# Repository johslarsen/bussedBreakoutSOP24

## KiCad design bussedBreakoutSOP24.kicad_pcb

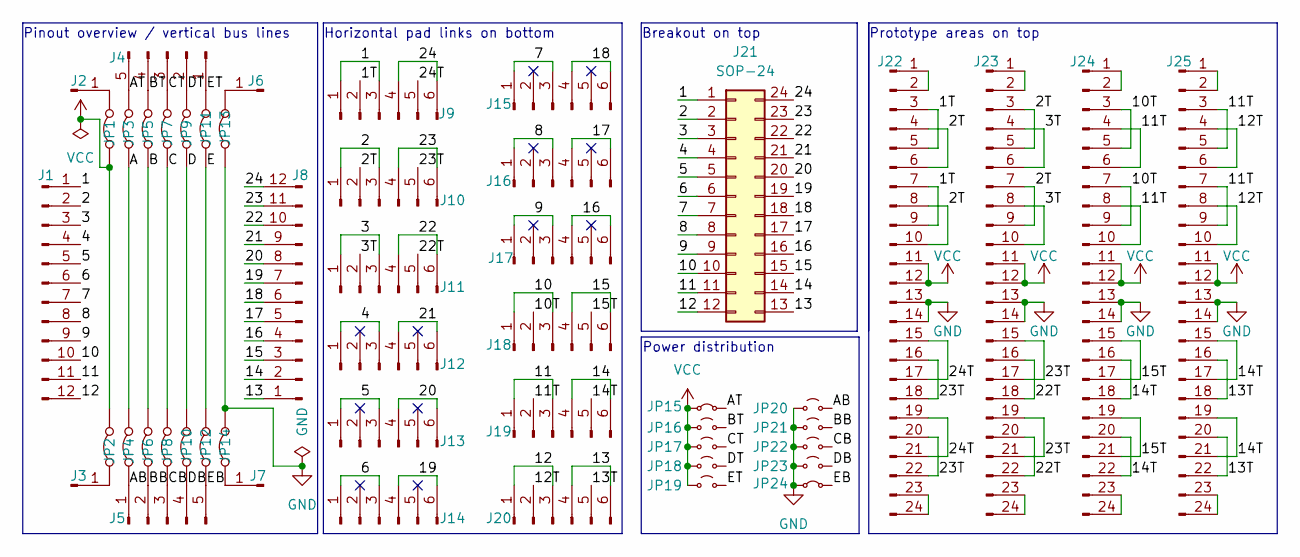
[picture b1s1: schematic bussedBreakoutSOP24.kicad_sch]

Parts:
J1, J8: Conn_01x12_Pin; Castellated_2x12
J2, J3, J6, J7: Conn_01x01_Pin; Castellated_corner
J4, J5: Conn_01x05_Pin; Castellated_2x05
J9, J10, J11, J12, J13, J14, J15, J16, J17, J18, J19, J20: Conn_01x06_Pin; SMD_0805_grid_1x6
J21: SOP-24; SOP-24_3.9-7.5mmx15.4mm_P1.27mm
J22, J23, J24, J25: Conn_01x24_Pin; SMD_grid_2x12_0402
JP1, JP2, JP3, JP4, JP5, JP6, JP7, JP8, JP9, JP10, JP11, JP12, JP13, JP14: Jumper_2_Bridged; SolderJumper-2_0402_Bridged_Unmarked
JP15, JP24: Jumper_2_Small_Bridged; SolderJumper-2_0402_Bridged_Unmarked
JP16, JP17, JP18, JP19, JP20, JP21, JP22, JP23: Jumper_2_Small_Open; SolderJumper-2_0402_Open_Unmarked

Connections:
/1: J1.1, J9.1, J9.3, J21.1
/1T: J9.2, J22.3, J22.5, J22.7, J22.9
/2: J1.2, J10.1, J10.3, J21.2
/2T: J10.2, J22.4, J22.6, J22.8, J22.10, J23.3, J23.5, J23.7, J23.9
/3: J1.3, J11.1, J11.3, J21.3
/3T: J11.2, J23.4, J23.6, J23.8, J23.10
/4: J1.4, J12.1, J12.3, J21.4
/5: J1.5, J13.1, J13.3, J21.5
/6: J1.6, J14.1, J14.3, J21.6
/7: J1.7, J15.1, J15.3, J21.7
/8: J1.8, J16.1, J16.3, J21.8
/9: J1.9, J17.1, J17.3, J21.9
/10: J1.10, J18.1, J18.3, J21.10
/10T: J18.2, J24.3, J24.5, J24.7, J24.9
/11: J1.11, J19.1, J19.3, J21.11
/11T: J19.2, J24.4, J24.6, J24.8, J24.10, J25.3, J25.5, J25.7, J25.9
/12: J1.12, J20.1, J20.3, J21.12
/12T: J20.2, J25.4, J25.6, J25.8, J25.10
/13: J8.1, J20.4, J20.6, J21.13
/13T: J20.5, J25.16, J25.18, J25.20, J25.22
/14: J8.2, J19.4, J19.6, J21.14
/14T: J19.5, J24.16, J24.18, J24.20, J24.22, J25.15, J25.17, J25.19, J25.21
/15: J8.3, J18.4, J18.6, J21.15
/15T: J18.5, J24.15, J24.17, J24.19, J24.21
/16: J8.4, J17.4, J17.6, J21.16
/17: J8.5, J16.4, J16.6, J21.17
/18: J8.6, J15.4, J15.6, J21.18
/19: J8.7, J14.4, J14.6, J21.19
/20: J8.8, J13.4, J13.6, J21.20
/21: J8.9, J12.4, J12.6, J21.21
/22: J8.10, J11.4, J11.6, J21.22
/22T: J11.5, J23.16, J23.18, J23.20, J23.22
/23: J8.11, J10.4, J10.6, J21.23
/23T: J10.5, J22.16, J22.18, J22.20, J22.22, J23.15, J23.17, J23.19, J23.21
/24: J8.12, J9.4, J9.6, J21.24
/24T: J9.5, J22.15, J22.17, J22.19, J22.21
/A: JP3.1 (A), JP4.2 (B)
/AB: J5.1, JP4.1 (A), JP20.2 (B)
/AT: J4.5, JP3.2 (B), JP15.2 (B)
/B: JP5.1 (A), JP6.2 (B)
/BB: J5.2, JP6.1 (A), JP21.2 (B)
/BT: J4.4, JP5.2 (B), JP16.2 (B)
/C: JP7.1 (A), JP8.2 (B)
/CB: J5.3, JP8.1 (A), JP22.2 (B)
/CT: J4.3, JP7.2 (B), JP17.2 (B)
/D: JP9.1 (A), JP10.2 (B)
/DB: J5.4, JP10.1 (A), JP23.2 (B)
/DT: J4.2, JP9.2 (B), JP18.2 (B)
/E: JP11.1 (A), JP12.2 (B)
/EB: J5.5, JP12.1 (A), JP24.2 (B)
/ET: J4.1, JP11.2 (B), JP19.2 (B)
GND: J22.13, J22.14, J23.13, J23.14, J24.13, J24.14, J25.13, J25.14, JP13.1 (A), JP14.2 (B), JP20.1 (A), JP21.1 (A), JP22.1 (A), JP23.1 (A), JP24.1 (A)
unnamed: J2.1, JP1.2 (B)
unnamed: J3.1, JP2.1 (A)
unnamed: J6.1, JP13.2 (B)
unnamed: J7.1, JP14.1 (A)
unnamed: J22.1, J22.2
unnamed: J22.23, J22.24
unnamed: J23.1, J23.2
unnamed: J23.23, J23.24
unnamed: J24.1, J24.2
unnamed: J24.23, J24.24
unnamed: J25.1, J25.2
unnamed: J25.23, J25.24
VCC: J22.11, J22.12, J23.11, J23.12, J24.11, J24.12, J25.11, J25.12, JP1.1 (A), JP2.2 (B), JP15.1 (A), JP16.1 (A), JP17.1 (A), JP18.1 (A), JP19.1 (A)

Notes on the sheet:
Pinout overview / vertical bus lines
Power distribution
Prototype areas on top
Horizontal pad links on bottom
Breakout on top

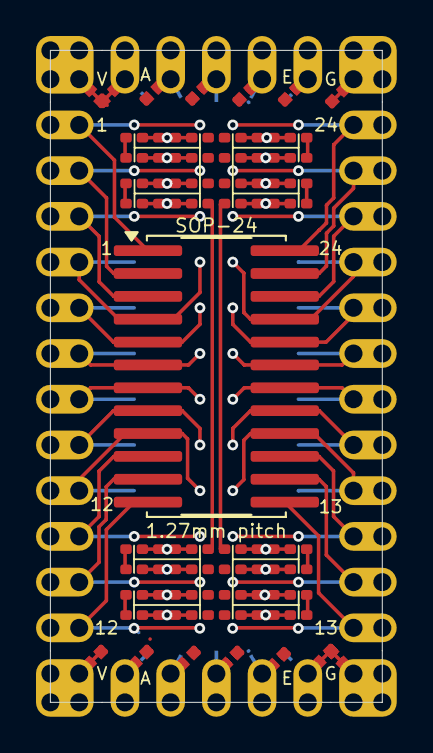
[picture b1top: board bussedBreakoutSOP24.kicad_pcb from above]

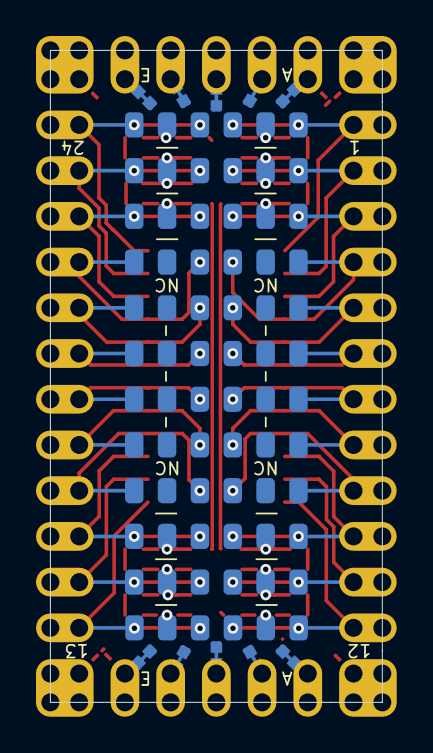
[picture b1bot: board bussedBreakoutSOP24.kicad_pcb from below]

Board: 2 copper layers, 18.4 x 36.2 mm, 49 parts (26 on the bottom side), 65 nets.

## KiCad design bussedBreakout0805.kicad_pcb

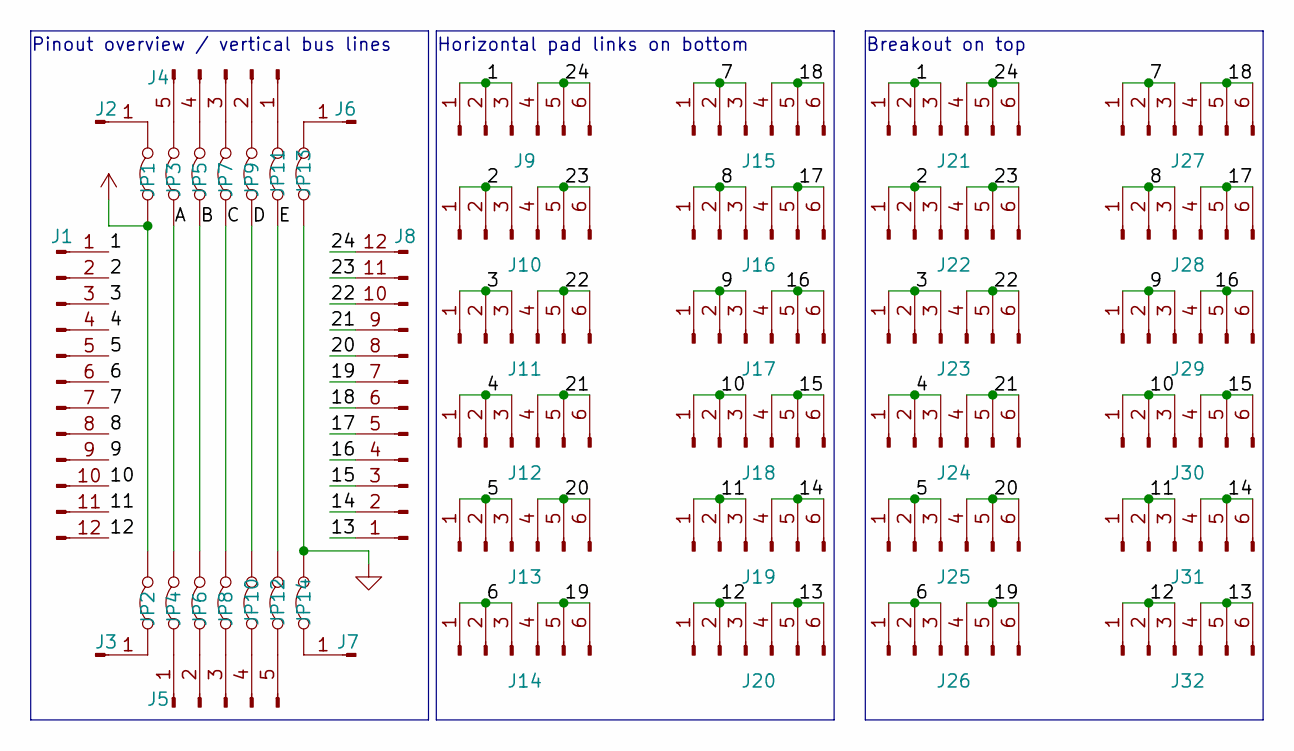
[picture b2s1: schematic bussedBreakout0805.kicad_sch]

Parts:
J1, J8: Conn_01x12_Pin; Castellated_2x12
J2, J3, J6, J7: Conn_01x01_Pin; Castellated_corner
J4, J5: Conn_01x05_Pin; Castellated_2x05
J9, J10, J11, J12, J13, J14, J15, J16, J17, J18, J19, J20, J21, J22, J23, J24, J25, J26, J27, J28, J29, J30, J31, J32: Conn_01x06_Pin; SMD_0805_grid_1x6
JP1, JP2, JP3, JP4, JP5, JP6, JP7, JP8, JP9, JP10, JP11, JP12, JP13, JP14: Jumper_2_Bridged; SolderJumper-2_0402_Bridged_Unmarked

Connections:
/1: J1.1, J9.1, J9.2, J9.3, J21.1, J21.2, J21.3
/2: J1.2, J10.1, J10.2, J10.3, J22.1, J22.2, J22.3
/3: J1.3, J11.1, J11.2, J11.3, J23.1, J23.2, J23.3
/4: J1.4, J12.1, J12.2, J12.3, J24.1, J24.2, J24.3
/5: J1.5, J13.1, J13.2, J13.3, J25.1, J25.2, J25.3
/6: J1.6, J14.1, J14.2, J14.3, J26.1, J26.2, J26.3
/7: J1.7, J15.1, J15.2, J15.3, J27.1, J27.2, J27.3
/8: J1.8, J16.1, J16.2, J16.3, J28.1, J28.2, J28.3
/9: J1.9, J17.1, J17.2, J17.3, J29.1, J29.2, J29.3
/10: J1.10, J18.1, J18.2, J18.3, J30.1, J30.2, J30.3
/11: J1.11, J19.1, J19.2, J19.3, J31.1, J31.2, J31.3
/12: J1.12, J20.1, J20.2, J20.3, J32.1, J32.2, J32.3
/13: J8.1, J20.4, J20.5, J20.6, J32.4, J32.5, J32.6
/14: J8.2, J19.4, J19.5, J19.6, J31.4, J31.5, J31.6
/15: J8.3, J18.4, J18.5, J18.6, J30.4, J30.5, J30.6
/16: J8.4, J17.4, J17.5, J17.6, J29.4, J29.5, J29.6
/17: J8.5, J16.4, J16.5, J16.6, J28.4, J28.5, J28.6
/18: J8.6, J15.4, J15.5, J15.6, J27.4, J27.5, J27.6
/19: J8.7, J14.4, J14.5, J14.6, J26.4, J26.5, J26.6
/20: J8.8, J13.4, J13.5, J13.6, J25.4, J25.5, J25.6
/21: J8.9, J12.4, J12.5, J12.6, J24.4, J24.5, J24.6
/22: J8.10, J11.4, J11.5, J11.6, J23.4, J23.5, J23.6
/23: J8.11, J10.4, J10.5, J10.6, J22.4, J22.5, J22.6
/24: J8.12, J9.4, J9.5, J9.6, J21.4, J21.5, J21.6
/A: JP3.1 (A), JP4.2 (B)
/B: JP5.1 (A), JP6.2 (B)
/C: JP7.1 (A), JP8.2 (B)
/D: JP9.1 (A), JP10.2 (B)
/E: JP11.1 (A), JP12.2 (B)
GND: JP13.1 (A), JP14.2 (B)
unnamed: J2.1, JP1.2 (B)
unnamed: J3.1, JP2.1 (A)
unnamed: J4.1, JP11.2 (B)
unnamed: J4.2, JP9.2 (B)
unnamed: J4.3, JP7.2 (B)
unnamed: J4.4, JP5.2 (B)
unnamed: J4.5, JP3.2 (B)
unnamed: J5.1, JP4.1 (A)
unnamed: J5.2, JP6.1 (A)
unnamed: J5.3, JP8.1 (A)
unnamed: J5.4, JP10.1 (A)
unnamed: J5.5, JP12.1 (A)
unnamed: J6.1, JP13.2 (B)
unnamed: J7.1, JP14.1 (A)
VCC: JP1.1 (A), JP2.2 (B)

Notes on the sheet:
Pinout overview / vertical bus lines
Horizontal pad links on bottom
Breakout on top

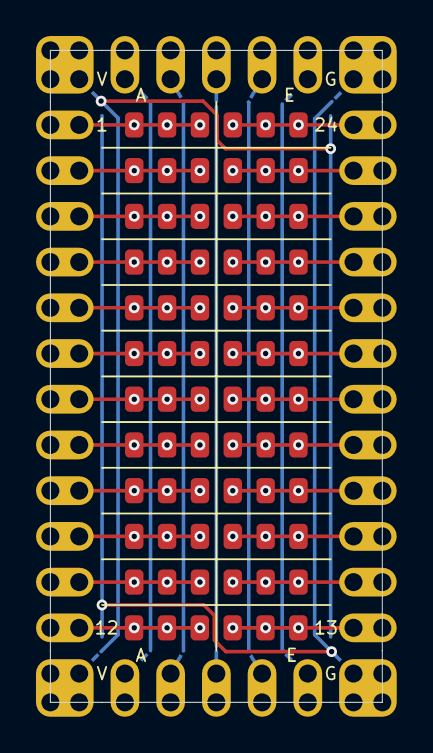
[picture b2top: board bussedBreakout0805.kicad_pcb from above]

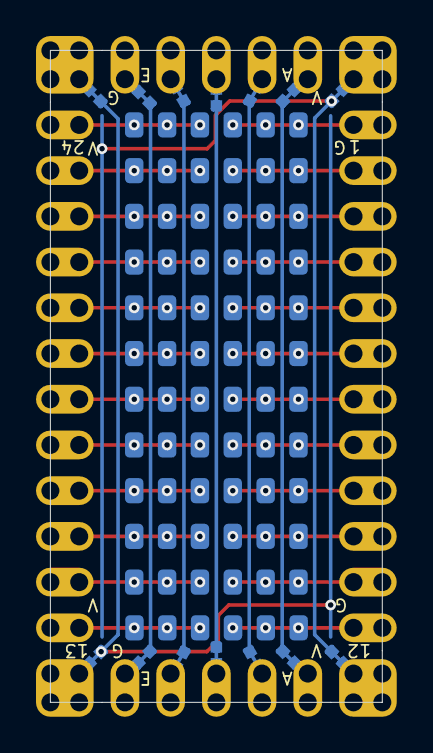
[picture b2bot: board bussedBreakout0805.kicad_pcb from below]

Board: 2 copper layers, 18.4 x 36.2 mm, 46 parts (30 on the bottom side), 45 nets.

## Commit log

2025-04-30 Release into public domain
2025-04-30 Initial concept with the bottom busses routed
2025-04-30 Add lib/SMD.pretty and lib/2.54mm_Pin_Headers.pretty submodules
2025-04-30 Routing completed
2025-04-30 Replace 1/3 of top 0805 footprints with twice as many 0402 ones
2025-04-30 Fix a misalgined bus bar, and add section indicators
2025-04-30 Add VCC/GND buses on opposite sides, add V[CC]/G[ND] labels, move labels away from solder mask cutouts
2025-04-30 Change to a SOP24 breakout
2025-04-30 Change to a SSOP-24 0.65mm pitch breakout
2025-04-30 Fix exposed bus bar on the bottom
2025-04-30 Add some prototyping area on the top
2025-04-30 Change to a custom SOP-24 footprint accomodating the narrowest 3.9mm to the widest 7.5mm SO-24 packages
2025-05-01 Change prototype area 0402s and connect it to VCC+GND+middle rows of pads on bottom
2025-05-01 Reoriente power distribution jumpers to remove GND/VCC routing workaround
2025-05-01 Add missing center pad separators on B.Silkscreen
2025-05-01 Fix/exclude DRC errors
